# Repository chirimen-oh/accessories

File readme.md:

# Accessories for CHIRIMEN

They are hardware accessories of CHIRIMEN, all open source blueprints and can be used on the CHIRIMEN environment. They are mainly intended for use with CHIRIMEN for RPi, but  general purpose and can be used in other environments.

- [prot-hat](forRaspberryPi3/prot-hat/)
- [rpi3GpioTester](forRaspberryPi3/rpi3GpioTester/)
- [Grove-adt7410](grove/adt7410/)
- [Grove-s11059](grove/s11059/)
- [RPi2SeinsmartRelayIF](others/RPi2SeinsmartRelayIF/)
- [dcfan-guide](others/dcfan-guide/)
- [neopixel_i2c_TH](others/neopixel_i2c_TH/)

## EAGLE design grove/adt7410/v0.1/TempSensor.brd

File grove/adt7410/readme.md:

# Temp Sensor for CHRMN

### OSHW 
- [OSHWA UID: JP000007](https://certification.oshwa.org/jp000007.html)

`Temp Sensor for CHRMN` is a ADT7410 temperature sensor board with Grove connector.

# Version

0.1

# License

CC by 4.0

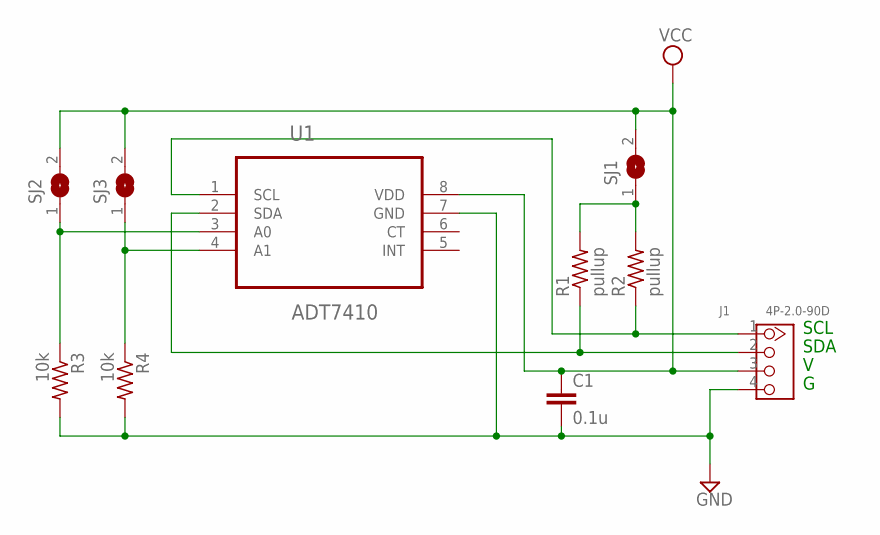
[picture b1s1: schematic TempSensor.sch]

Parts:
C1: 0.1u; C0603
J1: 4P-2.0-90D; HW4-2.0-90D
R1, R2: pullup; R0603
R3, R4: 10k; R0603
SJ1, SJ2, SJ3: SJ
U1: ADT7410; SOIC127P600X175-8N

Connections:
GND: C1.2, J1.4, R3.2, R4.2, U1.7 (GND)
unnamed: J1.1, R2.1, U1.1 (SCL)
unnamed: J1.2, R1.1, U1.2 (SDA)
unnamed: R1.2, R2.2, SJ1.1
unnamed: R4.1, SJ3.1, U1.4 (A1)
unnamed: R3.1, SJ2.1, U1.3 (A0)
VCC: C1.1, J1.3, SJ1.2, SJ2.2, SJ3.2, U1.8 (VDD)

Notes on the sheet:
SCL
SDA

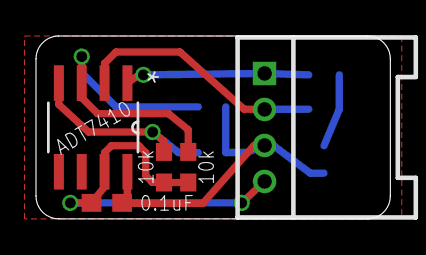
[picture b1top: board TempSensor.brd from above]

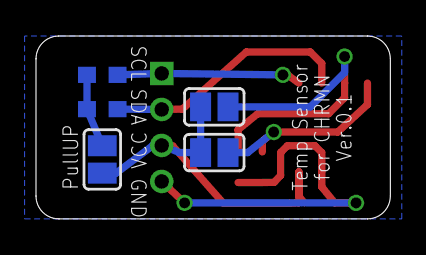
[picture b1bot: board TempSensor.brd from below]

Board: 2 copper layers, 19.7 x 10.2 mm, 10 parts (5 on the bottom side), 7 nets.

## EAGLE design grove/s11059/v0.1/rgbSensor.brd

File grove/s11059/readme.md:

# Temp Sensor for CHRMN

`RGB Sensor for CHRMN` is a S11059 RGB sensor board with Grove connector.

# Version

0.1

# License

CC by 4.0

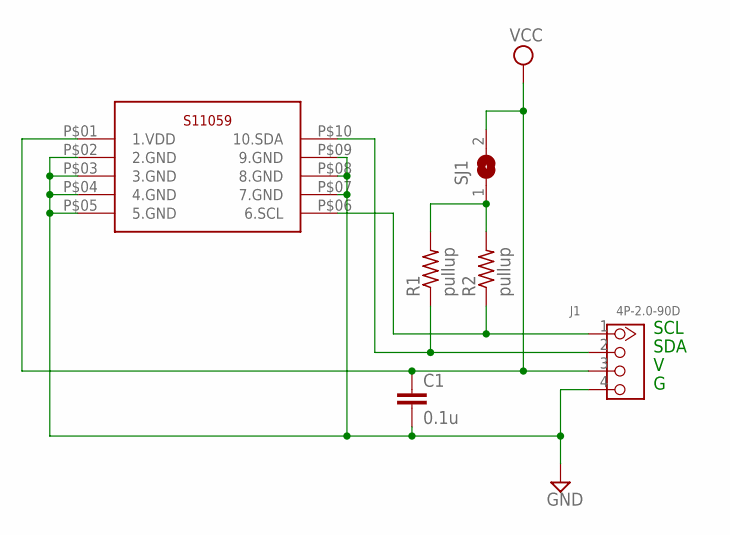
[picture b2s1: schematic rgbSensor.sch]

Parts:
C1: 0.1u; C0603
J1: 4P-2.0-90D; HW4-2.0-90D
R1, R2: pullup; R0603
SJ1: SJ
U$1: S11059; S11059-2DT

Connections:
GND: C1.2, J1.4, U$1.P$02 (2.GND), U$1.P$03 (3.GND), U$1.P$04 (4.GND), U$1.P$05 (5.GND), U$1.P$07 (7.GND), U$1.P$08 (8.GND), U$1.P$09 (9.GND)
unnamed: J1.2, R1.1, U$1.P$10 (10.SDA)
unnamed: R1.2, R2.2, SJ1.1
unnamed: J1.1, R2.1, U$1.P$06 (6.SCL)
VCC: C1.1, J1.3, SJ1.2, U$1.P$01 (1.VDD)

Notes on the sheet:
SCL
SDA

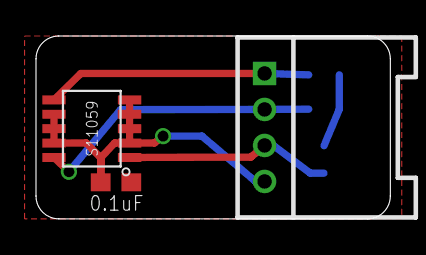
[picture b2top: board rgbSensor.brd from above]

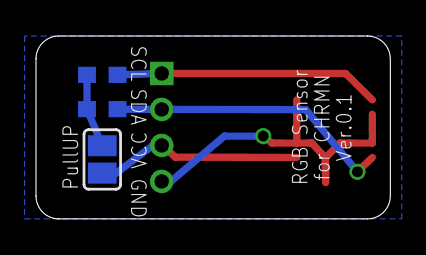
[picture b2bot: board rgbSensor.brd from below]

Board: 2 copper layers, 19.7 x 10.2 mm, 6 parts (3 on the bottom side), 5 nets.

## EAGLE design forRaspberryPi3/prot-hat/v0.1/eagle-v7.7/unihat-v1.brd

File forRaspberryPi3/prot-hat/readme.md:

# Prot-Hat for CHIRIMEN (Raspberry Pi 3)

`Prot-Hat for CHIRIMEN` is a `Hat` type prototyping board for Raspberry Pi 3.

# Version

0.1

# License

CC by 4.0

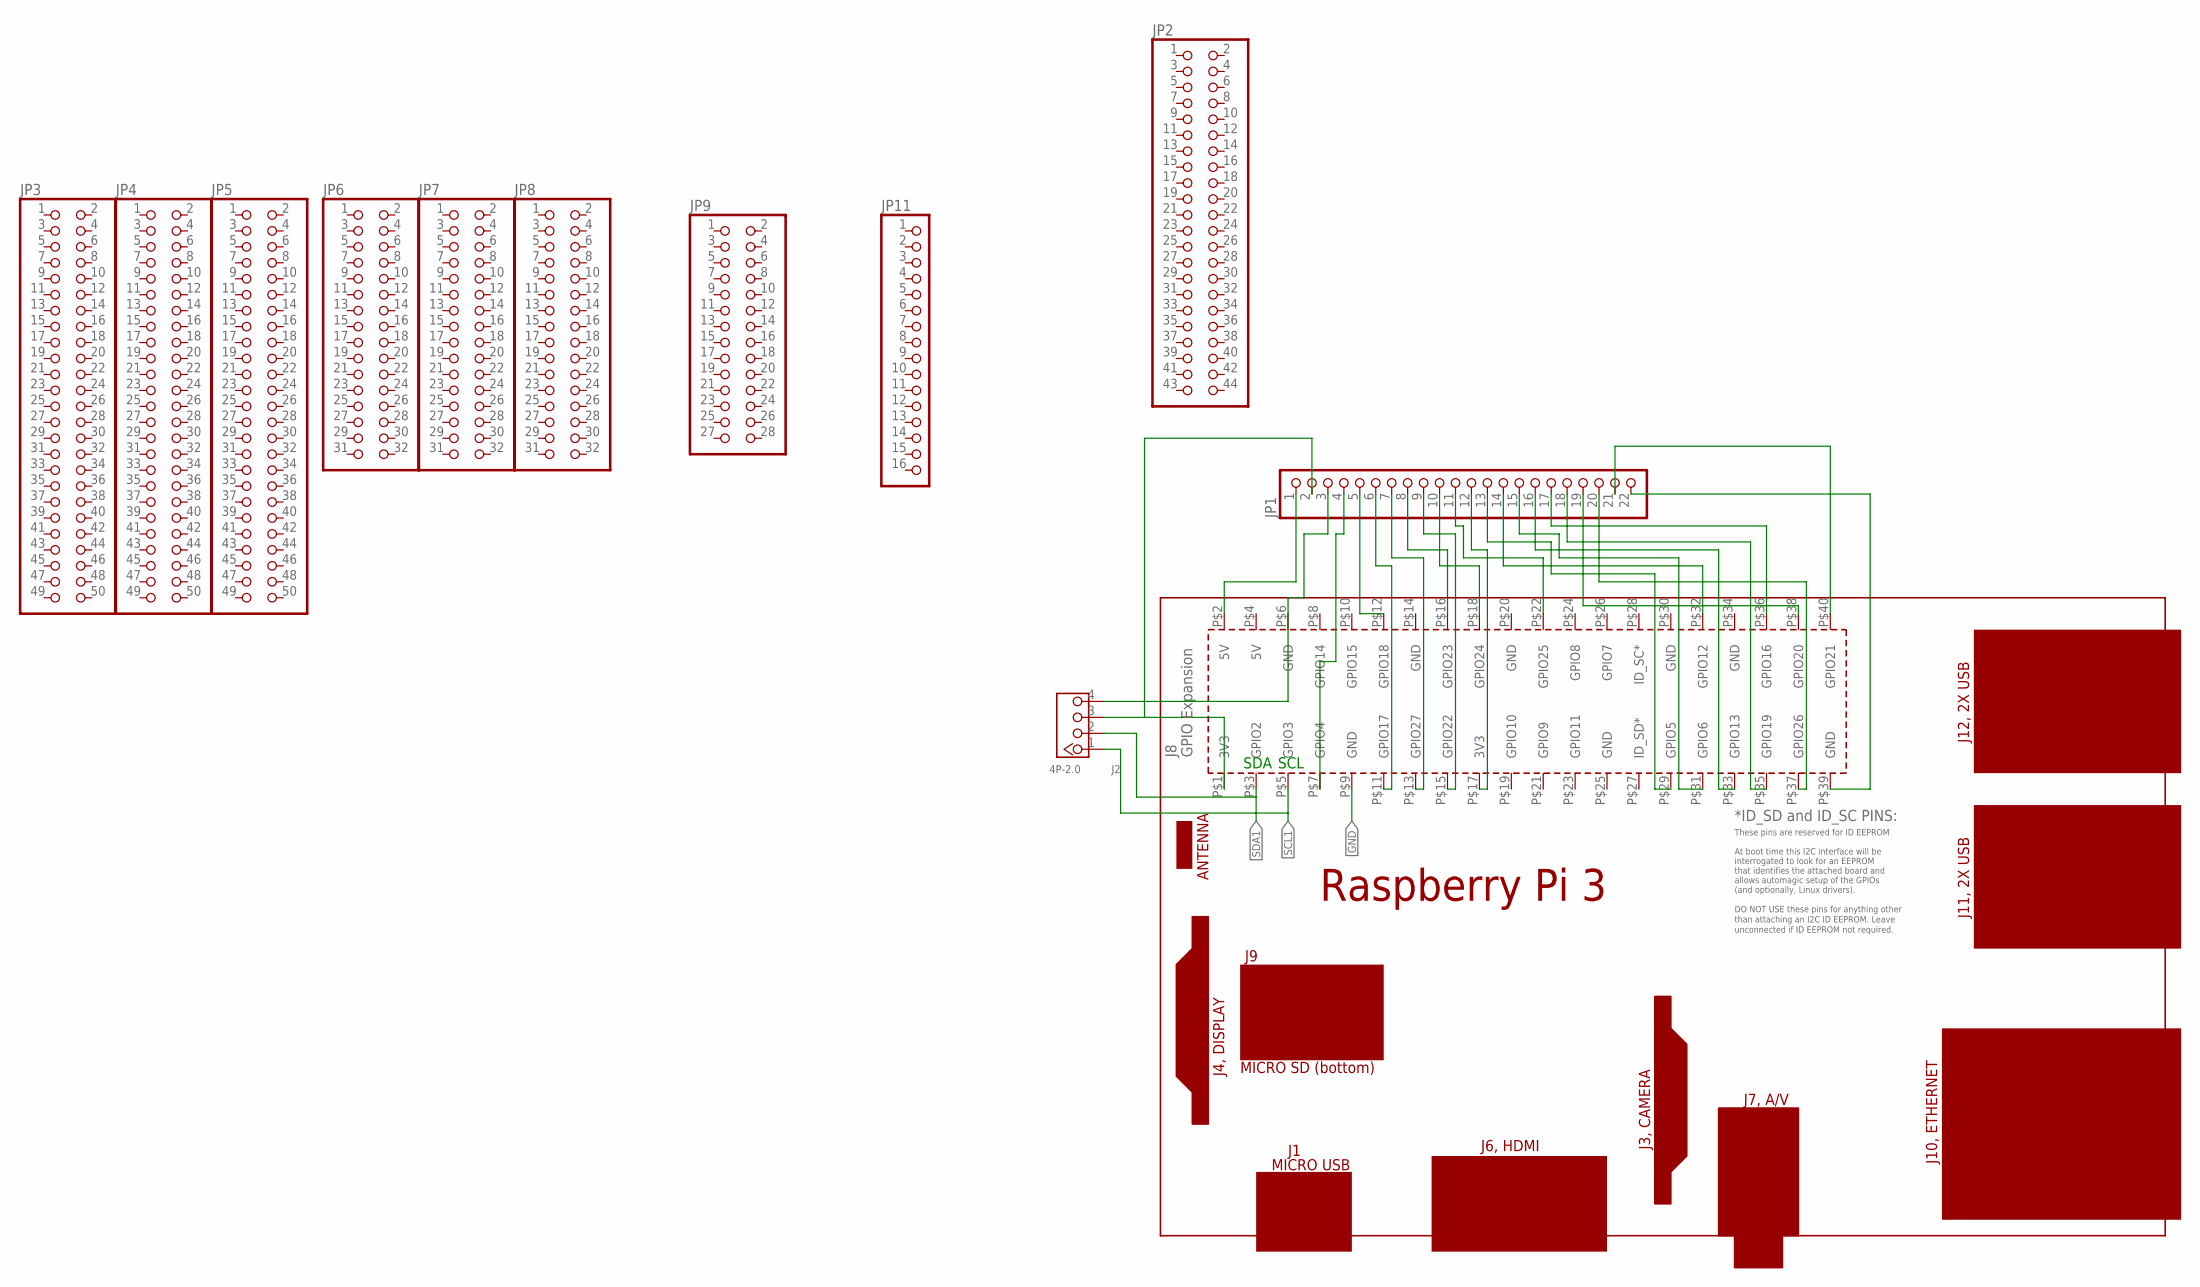
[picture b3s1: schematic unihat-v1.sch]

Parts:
J2: 4P-2.0; HW4-2.0
JP1: PINHD-1X22; 1X22
JP2: PINHD-2X22; 2X22
JP3, JP4, JP5: PINHD-2X25; 2X25
JP6, JP7, JP8: PINHD-2X16; 2X16
JP9: PINHD-2X14; 2X14
JP11: PINHD-1X16; 1X16
PCB1: RPI3

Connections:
GND: PCB1.P$9 (GND)
unnamed: JP1.5, PCB1.P$12 (GPIO18)
unnamed: JP1.1, PCB1.P$2 (5V)
unnamed: J2.3, JP1.2, PCB1.P$1 (3V3)
unnamed: J2.4, JP1.3, PCB1.P$6 (GND)
unnamed: JP1.4, PCB1.P$7 (GPIO4)
unnamed: JP1.6, PCB1.P$11 (GPIO17)
unnamed: JP1.7, PCB1.P$13 (GPIO27)
unnamed: JP1.8, PCB1.P$16 (GPIO23)
unnamed: JP1.9, PCB1.P$15 (GPIO22)
unnamed: JP1.10, PCB1.P$18 (GPIO24)
unnamed: JP1.11, PCB1.P$22 (GPIO25)
unnamed: JP1.13, PCB1.P$29 (GPIO5)
unnamed: JP1.12, PCB1.P$17 (3V3)
unnamed: JP1.14, PCB1.P$32 (GPIO12)
unnamed: JP1.15, PCB1.P$31 (GPIO6)
unnamed: JP1.16, PCB1.P$33 (GPIO13)
unnamed: JP1.17, PCB1.P$36 (GPIO16)
unnamed: JP1.18, PCB1.P$35 (GPIO19)
unnamed: JP1.19, PCB1.P$38 (GPIO20)
unnamed: JP1.20, PCB1.P$37 (GPIO26)
unnamed: JP1.21, PCB1.P$40 (GPIO21)
unnamed: JP1.22, PCB1.P$39 (GND)
SCL1: J2.1, PCB1.P$5 (GPIO3)
SDA1: J2.2, PCB1.P$3 (GPIO2)

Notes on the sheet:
SDA
SCL

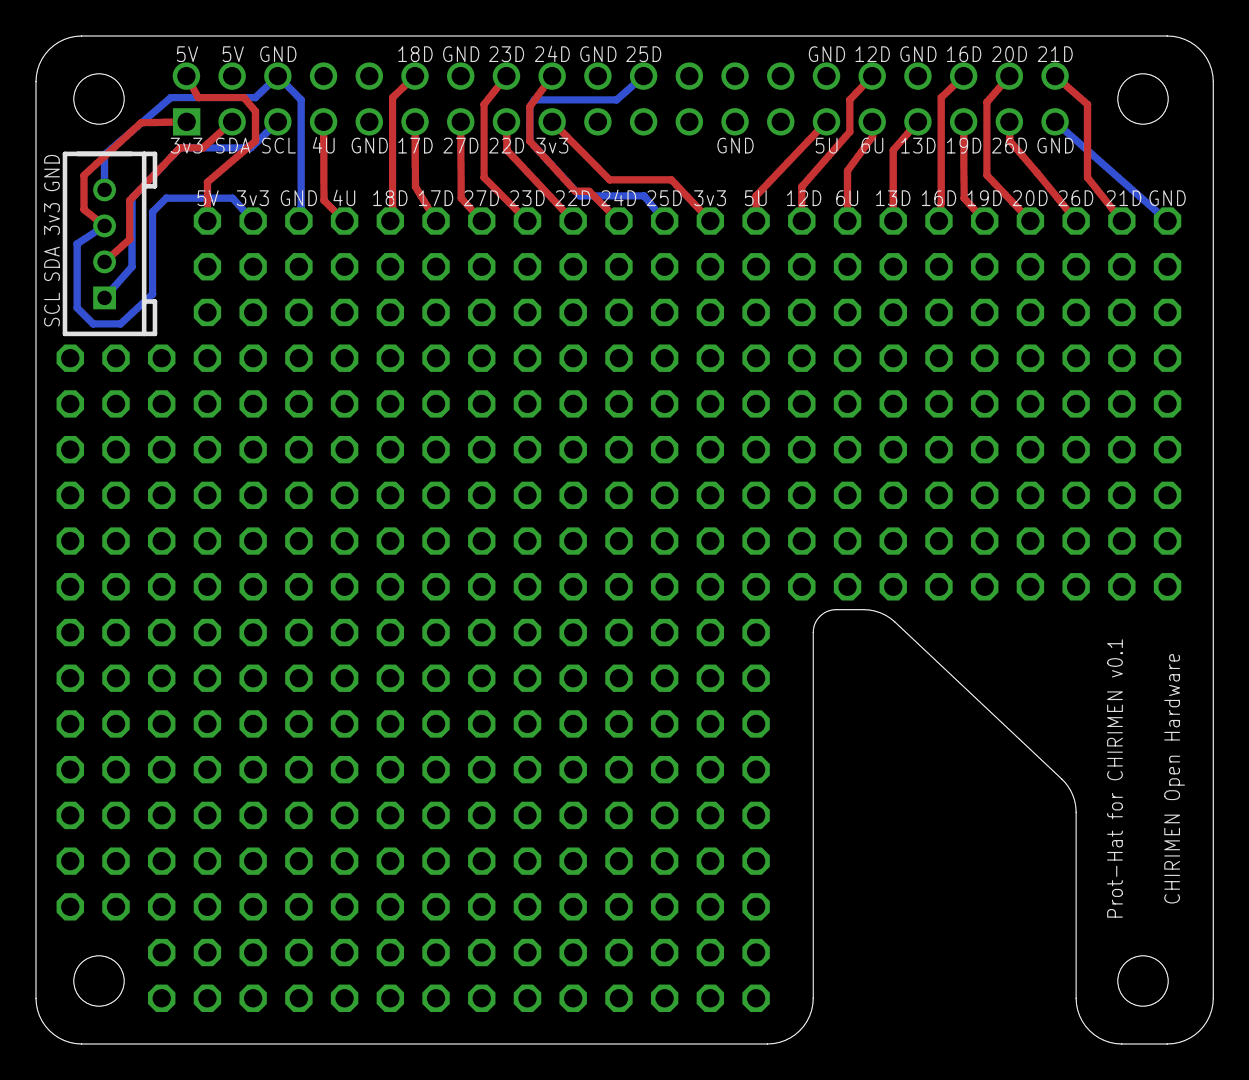
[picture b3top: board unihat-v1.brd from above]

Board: 2 copper layers, 65.4 x 56.0 mm, 12 parts (0 on the bottom side), 24 nets.

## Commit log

2017-12-04 add image
2018-02-28 add grove/adt7410 and grove/s11059
2018-07-10 add dcfan guide
2019-11-18 Update tester board
2019-11-20 Update rpi3GpioTester pcb design
2019-11-20 Board.png
2019-11-21 rpi3GpioTester rev0.3
2019-11-22 Add I2C pull up pattern
2019-11-22 Minor update
2019-11-25 Update rpi3GpioTester
2019-11-28 rpi3GpioTester 10x10cm design change...
2019-11-28 rpi3GpioTester minor change
2019-12-02 add parts list
2019-12-06 rpiGpioTester silk update
2019-12-15 chirimen test board photo
2019-12-15 rotate photo
2019-12-17 Add schematic img
2020-01-25 Create LICENSE
2020-01-25 Update LICENSE
2021-02-06 OSHWA UID add
2022-09-11 LED の色分けについて追記
2024-08-20 change link url
